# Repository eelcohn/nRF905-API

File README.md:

# nRF905 Arduino API
nRF905 Arduino API. Compatible with ESP8266 and ESP32 boards, tested on *Wemos D1 mini Pro*, *NodeMCU 1.0 (ESP-12E module)* and *DOIT ESP32 Dev Module*.

## Building the hardware
See [Buiding the hardware](https://github.com/eelcohn/nRF905-API/blob/master/HARDWARE.md)

## Compiling / Installing
1. Install the [Arduino IDE](https://www.arduino.cc/en/Main/Software)
2. Open the [nRF905API.ino](https://github.com/eelcohn/nRF905-API/blob/master/src/nRF905API/nRF905API.ino) file in Arduino IDE
3. In the *File* menu select *Preferences* and add the following to *Additional Board Manager URLs*:
```
https://arduino.esp8266.com/stable/package_esp8266com_index.json,https://dl.espressif.com/dl/package_esp32_index.json
```
4. In the *Tools* menu select *Board* and find the board you are using (DO-IT ESP32 / Wemos / NodeMCU etc).
5. In the *Sketch* menu select *Upload*
6. When the code has been uploaded the device will reboot and start a WiFi access point named `nRF905`. Connect to that access point with the password `nrf905api`.
7. Open a webbrowser and go to `http://192.168.4.1/`
8. Follow the configuration wizard:<br>
<br>
<br>
<br>
<br>
<br>
<br>
<br>
9. Your device will now connect to your WiFi network.

## Support

Due to lack of time it might take a long time for me to give support.

## Usage

### /api/v1/config.json
Configure the nRF905.

Example:<br>
`http://192.168.x.y/api/v1/config.json?frequency=868400000&crc=16&txpower=10&rxpower=normal&rxaddr=a55a5aa5&txaddr=a55a5aa5&rxaddrwidth=4&txaddrwidth=4&rxpayloadwidth=16&txpayloadwidth=16`

|  Parameter     | Required | Description |
|:--------------:|:--------:|:------------|
|  `frequency`   |    No    | Set the RF frequency |
|     `crc`      |    No    | `off`: disable CRC<br>`8`: enable 8-bit CRC<br>`16`: enable 16-bt CRC |
|   `txpower`    |    No    | Set the RF transmit power<br>`-10`: -10dBm<br>`-2`: -2dBm<br>`6`: 6dBm<br>`10`: 10dBm |
|   `rxpower`    |    No    | Set the RF receive power<br>`normal`: normal receive mode<br>`low`: low power receive mode |
| `txaddrwidth`  |    No    | Set the number of Tx address bytes<br>`1`: 1 byte<br>`4`: 4 bytes |
| `rxaddrwidth`  |    No    | Set the number of Rx address bytes<br>`1`: 1 byte<br>`4`: 4 bytes |
|`txpayloadwidth`|    No    | Set the number of Tx payload bytes<br>`1...32`: Payload is 1...32 bytes |
|`rxpayloadwidth`|    No    | Set the number of Rx payload bytes<br>`1...32`: Payload is 1...32 bytes |
|    `txaddr`    |    No    | Set the Tx address<br>`0x12345678`: Set Tx address to 0x12345678 |
|    `rxaddr`    |    No    | Set the Rx address<br>`0x12345678`: Set Rx address to 0x12345678 |
|    `nvram`     |    No    | Store the nRF905 configuration in NVRAM<br>`true`: Store nRF905 config in NVRAM<br>`false`: Do not store nRF905 config in NVRAM |

### /api/v1/status.json
This will show a status page with details about the hardware. This API call takes no parameters.

Example:<br>
`http://192.168.x.y/api/v1/status.json`

### /api/v1/receive.json
This will return a list of received data frames by the nRF905. This API call takes no parameters.

Example:<br>
`http://192.168.x.y/api/v1/receive.json`

### /api/v1/send.json
This will transmit data. After the data has been transmitted, the API will wait for data to be received (a reply to the transmitted data). By default it will wait for 2 seconds, but you can change this by adding the `timeout` parameter.

Example:<br>
`http://192.168.x.y/api/v1/send.json?txaddr=aabbccdd&payload=0400035efa0c04a55a5aa50000000000&timeout=10`

| Parameter | Required | Description |
|:---------:|:--------:|:------------|
| `txaddr`  |   Yes    | Address to send the data to |
| `payload` |   Yes    | The data to be sent |
| `timeout` |    No    | Timeout for reading data after the transmission is completed (in seconds)<br>Default: 2 seconds |

### /api/v1/systemconfig.json
Configure the system board.

Example:<br>
`http://192.168.x.y/api/v1/systemconfig.json?reset=true`

|  Parameter     | Required | Description |
|:--------------:|:--------:|:------------|
|    `reset `    |    No    | Reset the system<br>`true`: Reset system |
|    `nvram `    |    No    | Clear the NVRAM<br>`clear`: Clear the NVRAM |

## Fan API calls

### /api/v2/fan/link.json

Link the nRF905-API to a fan device. This API call takes no parameters.

Example:<br>
`http://192.168.x.y/api/v2/fan/link.json`

### /api/v2/fan/config.json

Configure the fan parameters.

Example:<br>
`http://192.168.x.y/api/v2/fan/config.json?model=zehnder&network=1a2b3c4d&main_unit_id=91&device_id=5d`

|  Parameter     | Required | Description |
|:--------------:|:--------:|:------------|
|    `model`     |   Yes    | Fan model:<br>`zehnder`: Zehnder fans (868.400MHz)<br>`buva`: BUVA fans (868.200MHz) |
|   `network`    |   Yes    | Network ID of your fan network |
| `main_unit_id` |   Yes    | ID of your fan main unit |
|  `device_id`   |   Yes    | ID of your nRF905-API |

### /api/v2/fan/setspeed.json

Set the fan speed of your fan device.

Example:<br>
`http://192.168.x.y/api/v2/fan/setspeed.json?speed=high`

|  Parameter     | Required | Description |
|:--------------:|:--------:|:------------|
|    `speed`     |   Yes    | Fan speed:<br>`low`: Low speed<br>`medium`: Medium speed<br>`high`: High speed<br>`max`: Maximum speed |
|    `timer`     |   No     | Set the fan timer (number of minutes) |

### /api/v2/fan/setvoltage.json

Set the fan voltage of your fan device.

Example:<br>
`http://192.168.x.y/api/v2/fan/setvoltage.json?voltage=2.4`

|  Parameter     | Required | Description |
|:--------------:|:--------:|:------------|
|   `voltage`    |   Yes    | Voltage:<br>`0.0`...`10.0`: Voltage; range between 0.0 volt and 10.0 volt |

### /api/test/fan/querydevice.json

Query a device for it's current settings (this API endpoint is not yet finished and is in test-mode).

Example:<br>
`http://192.168.x.y/api/test/fan/querydevice.json?device_id=32`

|  Parameter     | Required | Description |
|:--------------:|:--------:|:------------|
|  `device_id`   |   No     | Device ID:<br>ID of a fan device. By default it will select the fan it's linked to |

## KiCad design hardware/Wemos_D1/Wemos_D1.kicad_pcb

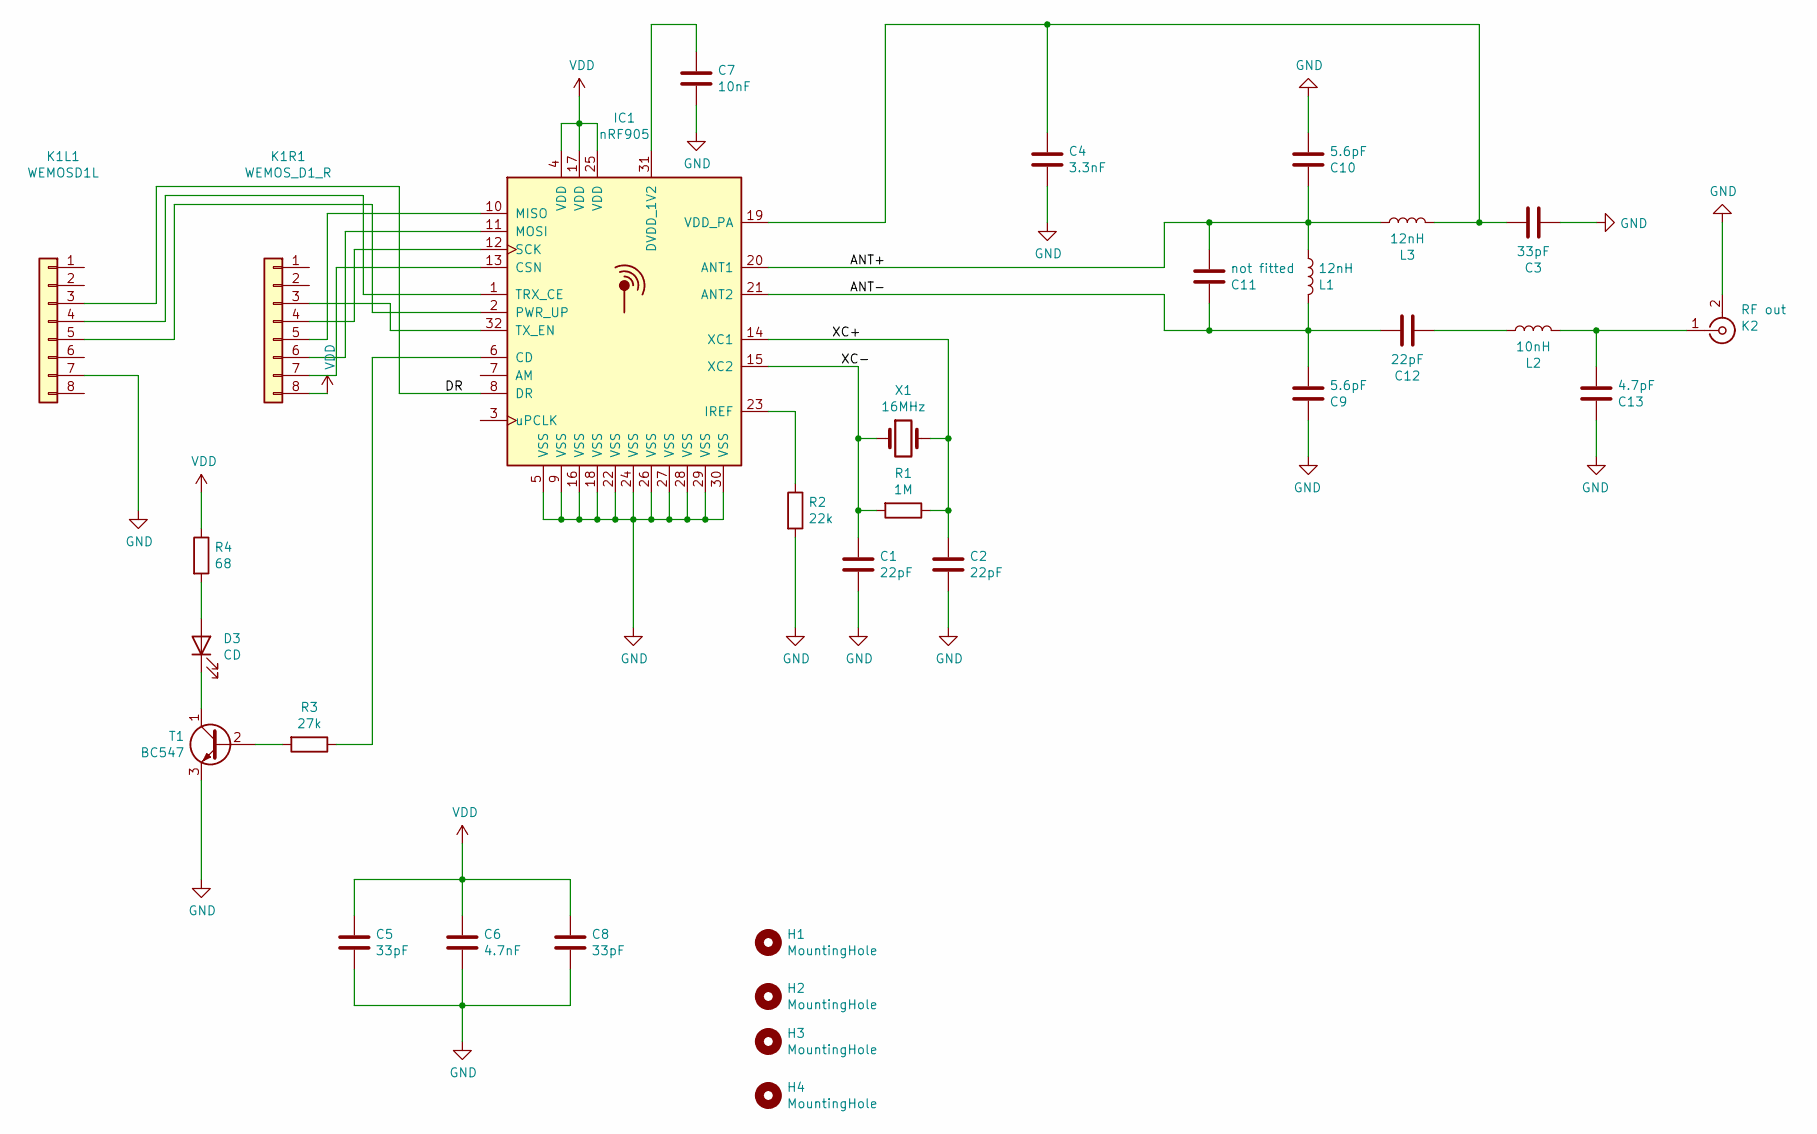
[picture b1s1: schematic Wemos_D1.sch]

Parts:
C1, C2, C12: 22pF; C_0603_1608Metric; Tolerance ±5%
C3, C5, C8: 33pF; C_0603_1608Metric; Tolerance ±5%
C4: 3.3nF; C_0603_1608Metric; Tolerance ±5%
C6: 4.7nF; C_0603_1608Metric; Tolerance ±5%
C7: 10nF; C_0603_1608Metric; Tolerance ±5%
C9, C10: 5.6pF; C_0603_1608Metric; Tolerance <±0.25pF
C11: not fitted; C_0603_1608Metric
C13: 4.7pF; C_0603_1608Metric; Tolerance ±5%
D3: CD; LED_0603_1608Metric; Forward Voltage 2V
H1, H2, H3, H4: MountingHole; MountingHole_3.2mm_M3_ISO14580
IC1: nRF905; TQFN-32-1EP_5x5mm_P0.5mm_EP2.1x2.1mm
K1L1: WEMOSD1L; PinSocket_1x08_P2.54mm_Vertical
K1R1: WEMOS_D1_R; PinSocket_1x08_P2.54mm_Vertical
K2: RF out; SMA_Amphenol_132134_Vertical
L1, L3: 12nH; L_0603_1608Metric; Tolerance ±5%
L2: 10nH; L_0603_1608Metric; Tolerance ±5%
R1: 1M; R_0603_1608Metric; Power Rating 0.1W; Tolerance ±5%
R2: 22k; R_0603_1608Metric; Power Rating 0.1W; Tolerance ±1%
R3: 27k; LED_0603_1608Metric; Tolerance 5%
R4: 68; LED_0603_1608Metric; Tolerance 5%
T1: BC547; SOT-323_SC-70
X1: 16MHz; Crystal_HC49-4H_Vertical

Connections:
/ANT+: C10.1, C11.2, IC1.20 (ANT1), L1.2, L3.2
/ANT-: C9.2, C11.1, C12.2, IC1.21 (ANT2), L1.1
/DR: IC1.8 (DR), K1L1.3; also elsewhere on the board
/XC+: C2.1, IC1.14 (XC1), R1.1, X1.2
/XC-: C1.1, IC1.15 (XC2), R1.2, X1.1
GND: C1.2, C2.2, C3.1, C4.2, C5.2, C6.2, C7.2, C8.2, C9.1, C10.2, C13.1, IC1.5 (VSS), IC1.9 (VSS), IC1.16 (VSS), IC1.18 (VSS), IC1.22 (VSS), IC1.24 (VSS), IC1.26 (VSS), IC1.27 (VSS), IC1.28 (VSS), IC1.29 (VSS), IC1.30 (VSS), IC1.33, K1L1.7, K2.2 (Ext), R2.2, T1.3 (E); also elsewhere on the board
unnamed: C3.2, C4.1, IC1.19 (VDD_PA), L3.1
unnamed: C7.1, IC1.31 (DVDD_1V2)
unnamed: C12.1, L2.2
unnamed: C13.2, K2.1 (In), L2.1
unnamed: D3.1 (K), T1.1 (C)
unnamed: D3.2 (A), R4.2
unnamed 12: IC1.1 (TRX_CE), K1L1.4; also elsewhere on the board
unnamed 13: IC1.2 (PWR_UP), K1L1.5; also elsewhere on the board
unnamed: IC1.6 (CD), R3.1
unnamed 17: IC1.10 (MISO), K1R1.5; also elsewhere on the board
unnamed 18: IC1.11 (MOSI), K1R1.6; also elsewhere on the board
unnamed 19: IC1.12 (SCK), K1R1.4; also elsewhere on the board
unnamed 20: IC1.13 (CSN), K1R1.7; also elsewhere on the board
unnamed: IC1.23 (IREF), R2.1
unnamed 22: IC1.32 (TX_EN), K1R1.3; also elsewhere on the board
unnamed: R3.2, T1.2 (B)
VDD: C5.1, C6.1, C8.1, IC1.4 (VDD), IC1.17 (VDD), IC1.25 (VDD), K1R1.8, R4.1; also elsewhere on the board

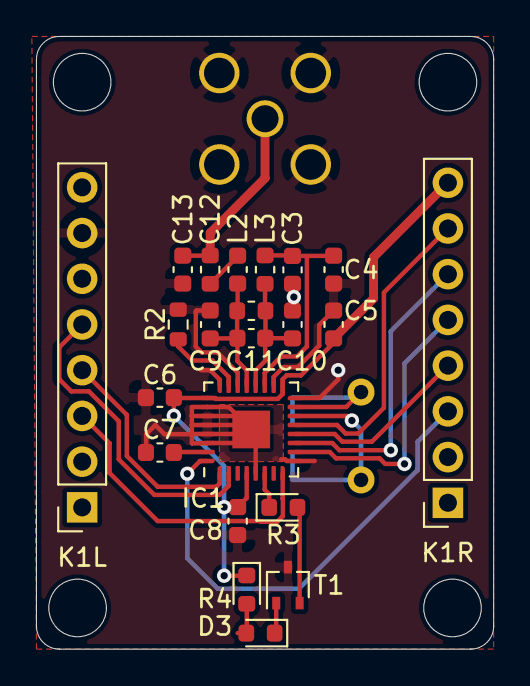
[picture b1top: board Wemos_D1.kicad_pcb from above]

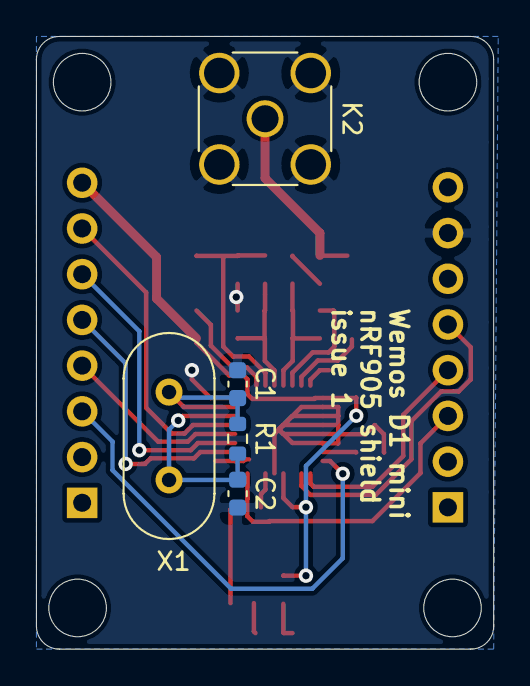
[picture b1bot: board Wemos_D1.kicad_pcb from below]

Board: 2 copper layers, 25.4 x 34.0 mm, 31 parts (5 on the bottom side), 23 nets.

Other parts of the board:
K1L: WEMOSD1L; PinSocket_1x08_P2.54mm_Vertical
K1R: WEMOS_D1_R; PinSocket_1x08_P2.54mm_Vertical

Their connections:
/DR: K1L.3; also elsewhere on the board
GND: K1L.7; also elsewhere on the board
unnamed 12: K1L.4; also elsewhere on the board
unnamed 13: K1L.5; also elsewhere on the board
unnamed 17: K1R.5; also elsewhere on the board
unnamed 18: K1R.6; also elsewhere on the board
unnamed 19: K1R.4; also elsewhere on the board
unnamed 20: K1R.7; also elsewhere on the board
unnamed 22: K1R.3; also elsewhere on the board
VDD: K1R.8; also elsewhere on the board

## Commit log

2020-03-29 v0.2.1 - First public release
2020-03-31 Added Vcc and Gnd to pin connection list
2020-04-01 Updated to v0.3.1
2020-04-02 Updated to v0.3.2
2020-06-06 Set WiFi into station mode
    Set's wifi into station mode. This rstops the nodeMCU starting a open wifi network (FaryLink_XXX)
2020-10-05 Added Wemos D1 mini pinout images
2020-10-22 Updated to v1.0.0
2020-10-22 Added config wizard screenshots
2020-10-22 Updated installation manual
2020-11-07 SCN must be CSN
2020-11-17 Update HOMEASSISTANT.md
    Changed secret names after review by
2021-01-27 Update README.md
    - The board selection section is in the tools menu instead of the sketch menu.
2021-12-14 Added initial hardware designs
2024-07-04 Update fan.cpp - beta support for ComfoAir E300 RF
